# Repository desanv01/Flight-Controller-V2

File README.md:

<h1 align="center">Flight Controller V2</h1>

<p align="center">STM32H743 hardware adaptation and ArduPilot integration</p>

---

STM32H743VIT6 controller adapted from an open-hardware reference design for externally regulated power, a signal-only OpenESC interface, exact Nano-Fit integration and a pinned ArduPilot target. The repository preserves the hardware adaptation, firmware work and vendor engineering packages.

**Project contributor:** [Desan Vasu](https://github.com/desanv01). Project engineering activities were performed by Desan; physical fabrication was external. Documented development: 26 August–6 October 2026. These are evidence dates, not employment dates.

> **Current status:** Engineering prototype. Manufacturer data, a pinned firmware target and freshly built FCV2 bootloader/BIN/APJ are available; powered-board, sensor and flight qualification remain pending.

**Quick links:** [KiCad project](hardware/Flight%20Controller.kicad_pro) · [Schematic PDF](docs/exports/schematic.pdf) · [Manufacturing](fabrication/README.md) · [Development history](docs/development/timeline.md) · [Verification](docs/validation-status.md) · [Releases](https://github.com/desanv01/Flight-Controller-V2/releases)

V2 is derived from [upstream hardware](https://api.github.com/repositories/1095062995), archived commit `0a60da1767061623549253d3cef8649f93ea052c`. Its original hardware design and contributors are credited below.

---

## Table of contents

- [Features](#features)
- [Hardware specifications](#hardware-specifications)
- [Architecture](#architecture)
- [Pin mapping](#pin-mapping)
- [Board layout and wiring](#board-layout-and-wiring)
- [Development history](#development-history)
- [Design and manufacturing files](#design-and-manufacturing-files)
- [Getting started](#getting-started)
- [Firmware](#firmware)
- [Verification](#verification)
- [Repository structure](#repository-structure)
- [License and credits](#license-and-credits)

---

## Features

- Reference-derived STM32H743VIT6 hardware with two dissimilar IMUs
- ICM42688P on SPI6, BMI270 on SPI3 and BMP388 on I2C2
- External regulated POWER1 supply; USB remains data/debug only
- Onboard AP63205 supply path removed; four signal-only OpenESC outputs
- Exact Molex Nano-Fit 105311-1202 on an integral connector tab
- Analog OSD hardware retained, disabled by initial firmware defaults
- Pinned ArduPilot Copter 4.7.1 source and neutral FCV2 target
- Separate JLCPCB and PCBWay source/manufacturing snapshots

---

## Hardware specifications

<details>
<summary>Full specifications and engineering status</summary>

| Parameter | Value |
|---|---|
| MCU | STM32H743VIT6, LQFP100 |
| PCB | 6 copper layers, 1.60 mm nominal |
| Design tool | KiCad 10.0.6 |
| Primary IMU | ICM-42688-P |
| Secondary IMU | BMI270 |
| Barometer | BMP388 |
| Power | External regulated input; exact boundary in power-and-interfaces documentation |
| USB | Data/debug; external controller power required |
| Motor signals | 4 controlled outputs |
| CAN | Retained CAN hardware; runtime qualification pending |
| Storage | W25Q128 flash |
| Board body | 40.5 × 40.5 mm main body |
| Mounting | 30.5 × 30.5 mm M3 |
| Overall envelope | About 40.575 × 50.500 mm including connector tab (vendor record) |
| Clock | 8 MHz active oscillator; HSE bypass |
| Fabrication status | Engineering data available; vendor/physical qualification outstanding |

</details>

Specifications describe the design intent and source. Runtime capabilities require physical qualification; see [validation status](docs/validation-status.md).

---

## Architecture

```mermaid
flowchart LR
    POWER[External regulated supply] --> FC[STM32H743 flight controller]
    IMU[ICM42688P, BMI270 and BMP388] --> FC
    RC[CRSF receiver] --> FC
    GPS[External GNSS and compass] --> FC
    FC -->|Motor signals and ground| ESC[OpenESC]
    BAT[Battery and power distribution] --> ESC
    COMP[Separately powered companion] <-->|Advisory data interface| FC
    USB[USB data and debug] <--> FC
```

The controller owns stabilization, motor waveforms, arming and failsafe. Companion perception/navigation is advisory and separately powered. [Architecture and boundaries](docs/architecture.md).

---

## Pin mapping

Controlled J6 motor outputs map to PE14, PE13, PE11 and PE9 / TIM1. ICM42688P uses SPI6; BMI270 uses SPI3; BMP388 uses I2C2. [Resource matrix](docs/pin-mapping.md).

The [connector pin tables](docs/connector-pinouts.md) are generated from the exact public netlist. Do not infer connector numbering from another version or from an unlabelled photograph.

---

## Board layout and wiring

CAD renders above represent the published source, not photographs of tested hardware. [PCB layer and assembly exports](docs/exports/README.md) · [Power and interfaces](docs/power-and-interfaces.md) · [Bring-up procedure](docs/bring-up.md).

---

## Development history

The [timeline](docs/development/timeline.md) follows requirements, resource freeze, schematic capture, correction, placement, routing and manufacturing stages. Each milestone links its evidence and tag. Publication commits use their actual import date; historical dates remain in the records.

The [development archive](archive/README.md) preserves unique CAD experiments and engineering scripts, including failed approaches. Source fragments are labelled as fragments; no missing historical source state is fabricated.

---

## Design and manufacturing files

| Material | Location |
|---|---|
| Editable current KiCad source | [hardware/](hardware/README.md) |
| Browser-readable schematic and PCB drawings | [docs/exports/](docs/exports/README.md) |
| JLCPCB engineering source and assembly data | [fabrication/jlcpcb/](fabrication/jlcpcb/README.md) |
| PCBWay engineering source and assembly data | [fabrication/pcbway/](fabrication/pcbway/README.md) |
| Downloadable source-associated bundles | [Engineering releases](https://github.com/desanv01/Flight-Controller-V2/releases) |
| Historical sources and experiments | [Archive index](archive/README.md) |

Choose one version and vendor package as a complete set. Do not mix source, Gerbers, BOM or placement files across packages. New public manifests replace original private-package hashes after neutral naming and metadata changes.

---

## Getting started

1. Download or clone this repository.
2. Install KiCad 10 with its standard symbol, footprint and 3D libraries.
3. Open [Flight Controller.kicad_pro](hardware/Flight%20Controller.kicad_pro), then the root schematic and PCB.
4. Review [hardware instructions](hardware/README.md), [verification](docs/validation-status.md) and the correct [vendor package](fabrication/README.md).
5. Review the props-off [bring-up checklist](docs/bring-up.md) before any powered hardware work.

Build/flash guidance for the neutral FCV2 target is in [firmware/README.md](firmware/README.md). Keep initial runtime defaults and the unreserved board-ID limitation visible.

---

## Firmware

ArduPilot Copter 4.7.1 source is pinned to `dbe792162d06cab66c3475fd5556bf7a120f119e`. The [firmware directory](firmware/README.md) contains FCV2 target/defaults, reproducible build instructions, and the successful build logs, binary hashes and downloadable bootloader/BIN/APJ. Legacy upstream targets are historical; final EVT1 compatibility is not asserted.

---

## Verification

Fresh source checks: **14 October 2026**, KiCad **10.0.6**.

| Check | Result |
|---|---|
| ERC errors / warnings | 0 / 40 |
| DRC rule errors / warnings | 0 / 0 |
| Raw unconnected entries | 0 |
| Schematic parity issues | 0 |
| Physical qualification | Pending |

Publication metadata reconciliation removed the original 119 schematic/PCB parity warnings without changing pad, routing, placement, zone or outline geometry.

Ignored checker categories and warning dispositions are recorded in [validation status](docs/validation-status.md). EDA checks and a firmware build do not establish physical reliability or flight qualification.

---

## Repository structure

```text
hardware/       Current coherent KiCad source and libraries
firmware/       Target availability, configuration and build provenance
fabrication/    Vendor-specific source, assembly data and export instructions
docs/           Architecture, pinouts, development history and portfolio case study
media/          Exact-source CAD renders and layer views
verification/   Fresh native reports, corrections and exception evidence
tools/          Portable checking/export utilities
archive/        Recovered source states and indexed development experiments
```

---

## License and credits

Inherited upstream hardware source remains under [CERN-OHL-S-2.0](LICENSE). KiCad-derived libraries, ArduPilot and other third-party content retain their own notices. [Third-party notices](THIRD_PARTY_NOTICES.md).

Desan Vasu performed the project engineering activities; fabrication was external. [Contribution statement](CONTRIBUTIONS.md) · [Portfolio case study](docs/portfolio/case-study.md).

Reference projects: [ArduPilot](https://github.com/ArduPilot/ardupilot), [KiCad](https://www.kicad.org/), and the OpenESC/OpenRX ecosystem identified in the source records.

Related project: [Flight Controller V1](https://github.com/desanv01/Flight-Controller-V1).

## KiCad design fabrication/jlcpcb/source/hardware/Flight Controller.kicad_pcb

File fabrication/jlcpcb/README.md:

# Flight Controller V2 — JLCPCB engineering package

Status: engineering data available; physical qualification pending. Supplier construction/impedance, actual part sourcing, rotations and fabricated-article tests remain external.

## Source and fabrication

Exact source: `source/hardware/`. [Source manifest](source/source-manifest.json). [Fresh source checks](verification/summary.json). Regenerated neutral Gerbers/drills are in `fabrication/`; upload the Gerber/drill-only ZIP rather than a documentation archive. Technical source and electrical/placement geometry are preserved; visible naming and descriptive metadata were updated for publication.

## Assembly files

- [FC_EVT1-BOM.csv](assembly/reference/FC_EVT1-BOM.csv)
- [FC_EVT1-CPL-JLCPCB.csv](assembly/reference/FC_EVT1-CPL-JLCPCB.csv)
- [FC_EVT1-CPL-KiCad.csv](assembly/reference/FC_EVT1-CPL-KiCad.csv)
- [FC_EVT1-JLCPCB-BOM-FINAL.csv](assembly/FC_EVT1-JLCPCB-BOM-FINAL.csv)
- [FC_EVT1-JLCPCB-CPL-FINAL.csv](assembly/FC_EVT1-JLCPCB-CPL-FINAL.csv)
- [J12-HAND-INSTALL-BOM.csv](assembly/J12-HAND-INSTALL-BOM.csv)

For V2 JLCPCB, files ending BOM-FINAL and CPL-FINAL are the final reconciled SMT pair; J12 is separately hand-installed. Earlier raw/engineering files are preserved only for traceability.

Use this vendor's exact BOM and centroid. Confirm rotation and sourcing with the manufacturer. J12 in V1 is microSD; J12 in V2 is POWER1, so designators must not be transferred between versions. [Current connector nets](../../docs/connector-pinouts.md).

## Documentation

Readable neutral exports are in `exports/`. Historical manufacturer notes in `documents/` retain original technical intent but some file references predate publication restructuring; use this README and exact source manifest as the upload map. [Physical checklist](../../docs/bring-up.md).

## Definitive upload map

| Supplier field | Public file |
|---|---|
| PCB fabrication | [Gerber/drill-only ZIP](fabrication/Gerber-Drill-Upload.zip) |
| Assembly BOM | [FC_EVT1-JLCPCB-BOM-FINAL.csv](assembly/FC_EVT1-JLCPCB-BOM-FINAL.csv) |
| SMT placement | [FC_EVT1-JLCPCB-CPL-FINAL.csv](assembly/FC_EVT1-JLCPCB-CPL-FINAL.csv) |
| Assembly drawing | [Assembly PDF](exports/assembly.pdf) |
| Fabrication drawing | [Fabrication PDF](exports/fabrication.pdf) |
| Schematic | [Schematic PDF](exports/schematic.pdf) |

Fresh reconciliation: 51 BOM rows, 113 BOM references and 113 placement references. Placement-only references: zero. BOM-only references: `none`; these require the separate THT/manual instructions. [Pair report](verification/final-upload-pair.json).

Raw export files under `assembly/reference/` are retained for traceability and are not the supplier upload pair. Part sourcing/rotation/vendor CAM and physical qualification are still required.

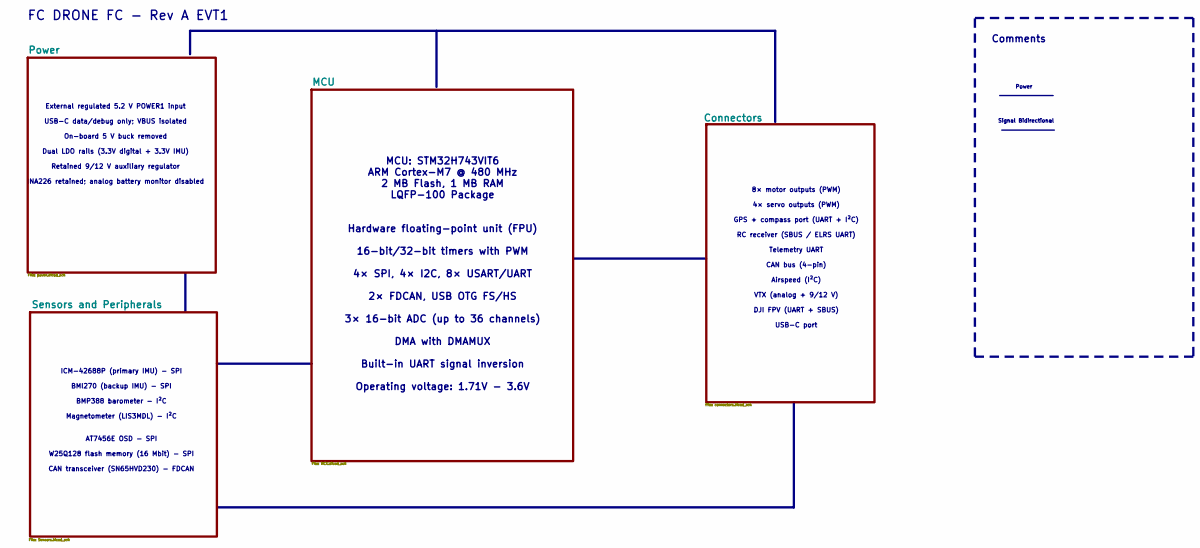
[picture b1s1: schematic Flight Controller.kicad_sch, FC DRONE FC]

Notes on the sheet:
FC DRONE FC - Rev A EVT1
ICM-42688P (primary IMU) - SPI BMI270 (backup IMU) - SPI BMP388 barometer - I²C Magnetometer (LIS3MDL) - I²C AT7456E OSD - SPI W25Q128 flash memory (16 Mbit) - SPI CAN transceiver (SN65HVD230) - FDCAN
Signal Bidirectional
8× motor outputs (PWM) 4× servo outputs (PWM) GPS + compass port (UART + I²C) RC receiver (SBUS / ELRS UART) Telemetry UART CAN bus (4-pin) Airspeed (I²C) VTX (analog + 9/12 V) DJI FPV (UART + SBUS) USB-C port
Comments
External regulated 5.2 V POWER1 input USB-C data/debug only; VBUS isolated On-board 5 V buck removed Dual LDO rails (3.3V digital + 3.3V IMU) Retained 9/12 V auxiliary regulator INA226 retained; analog battery monitor disabled
MCU: STM32H743VIT6 ARM Cortex-M7 @ 480 MHz 2 MB Flash, 1 MB RAM LQFP-100 Package Hardware floating-point unit (FPU) 16-bit/32-bit timers with PWM 4× SPI, 4× I2C, 8× USART/UART 2× FDCAN, USB OTG FS/HS 3× 16-bit ADC (up to 36 channels) DMA with DMAMUX Built-in UART signal inversion Operating voltage: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
Power

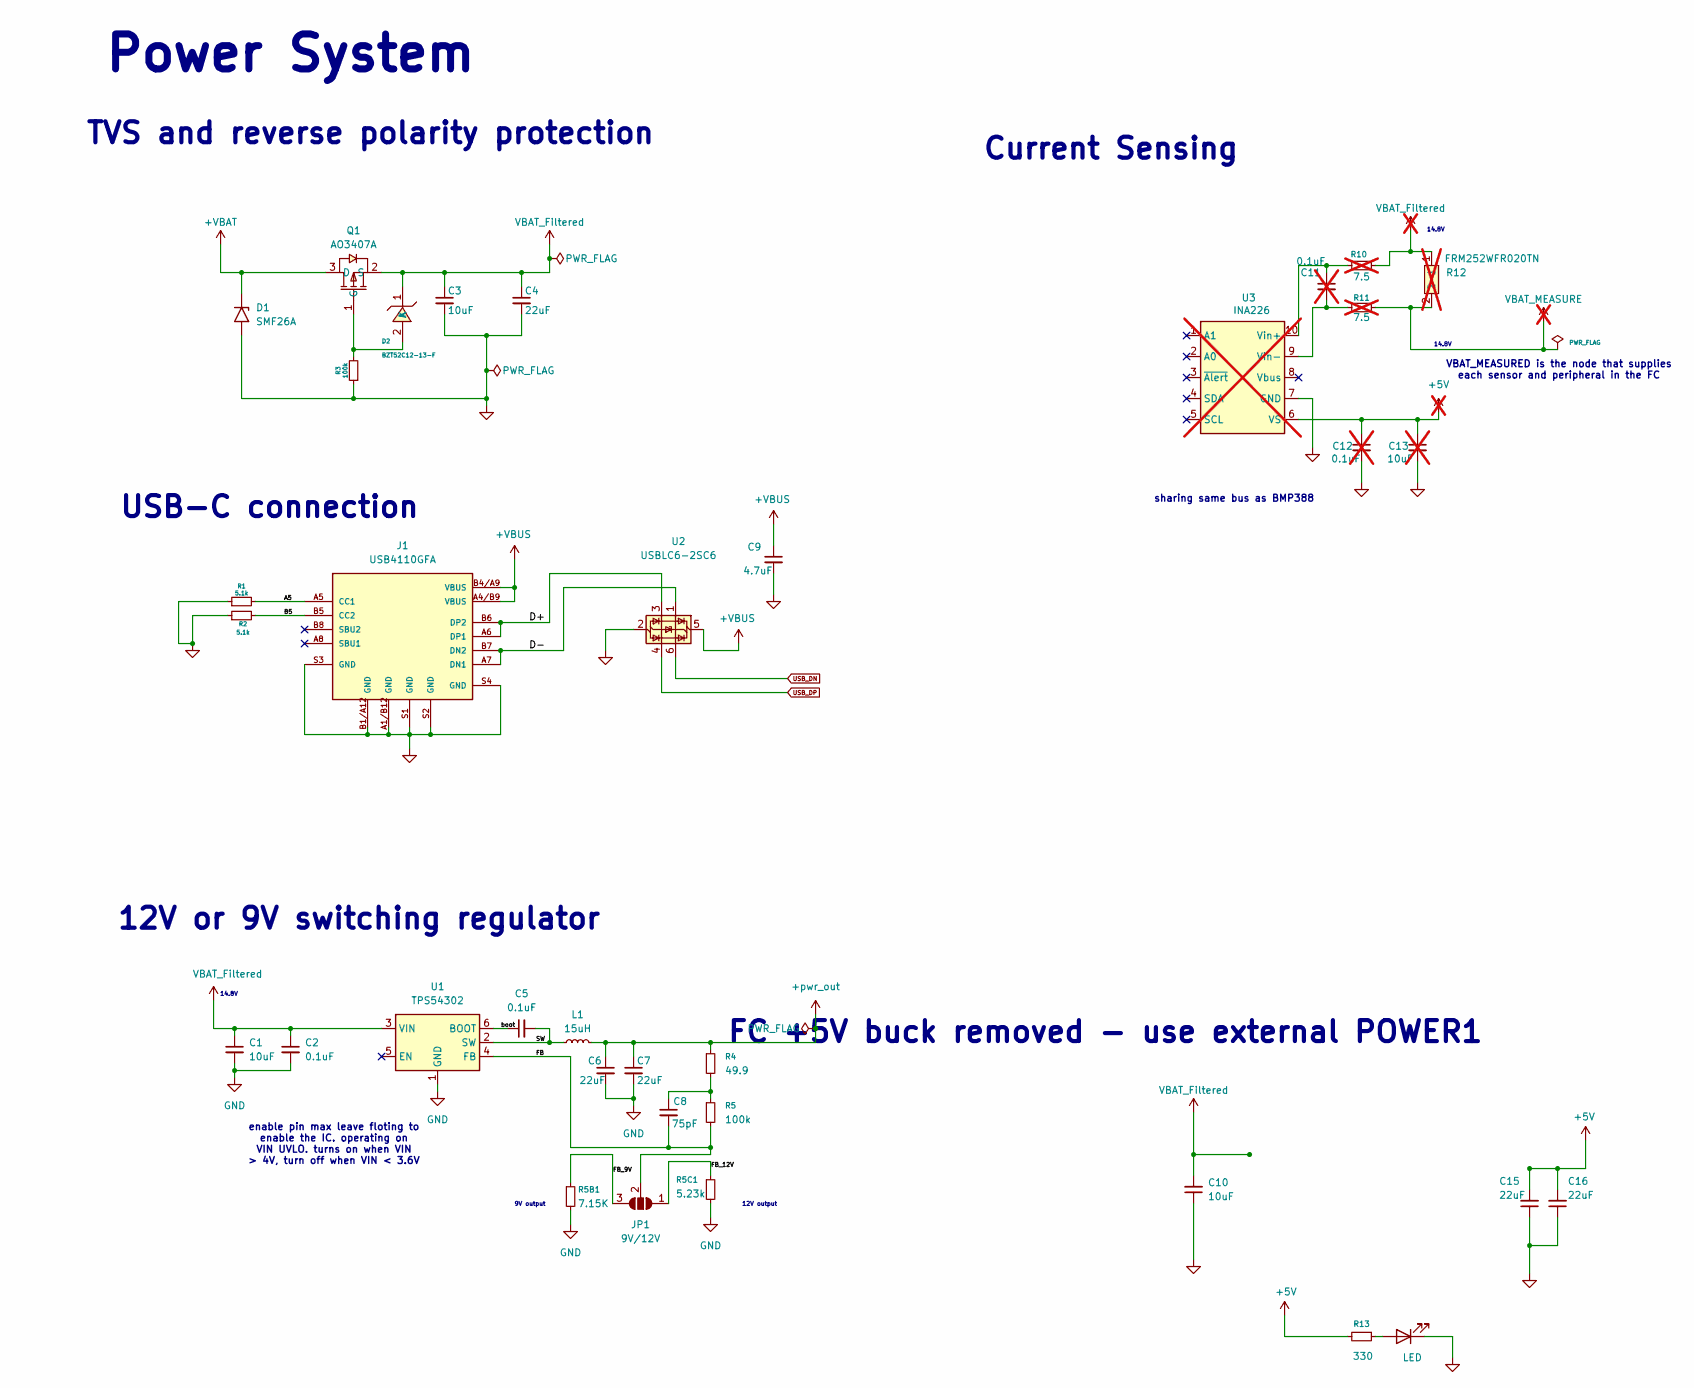
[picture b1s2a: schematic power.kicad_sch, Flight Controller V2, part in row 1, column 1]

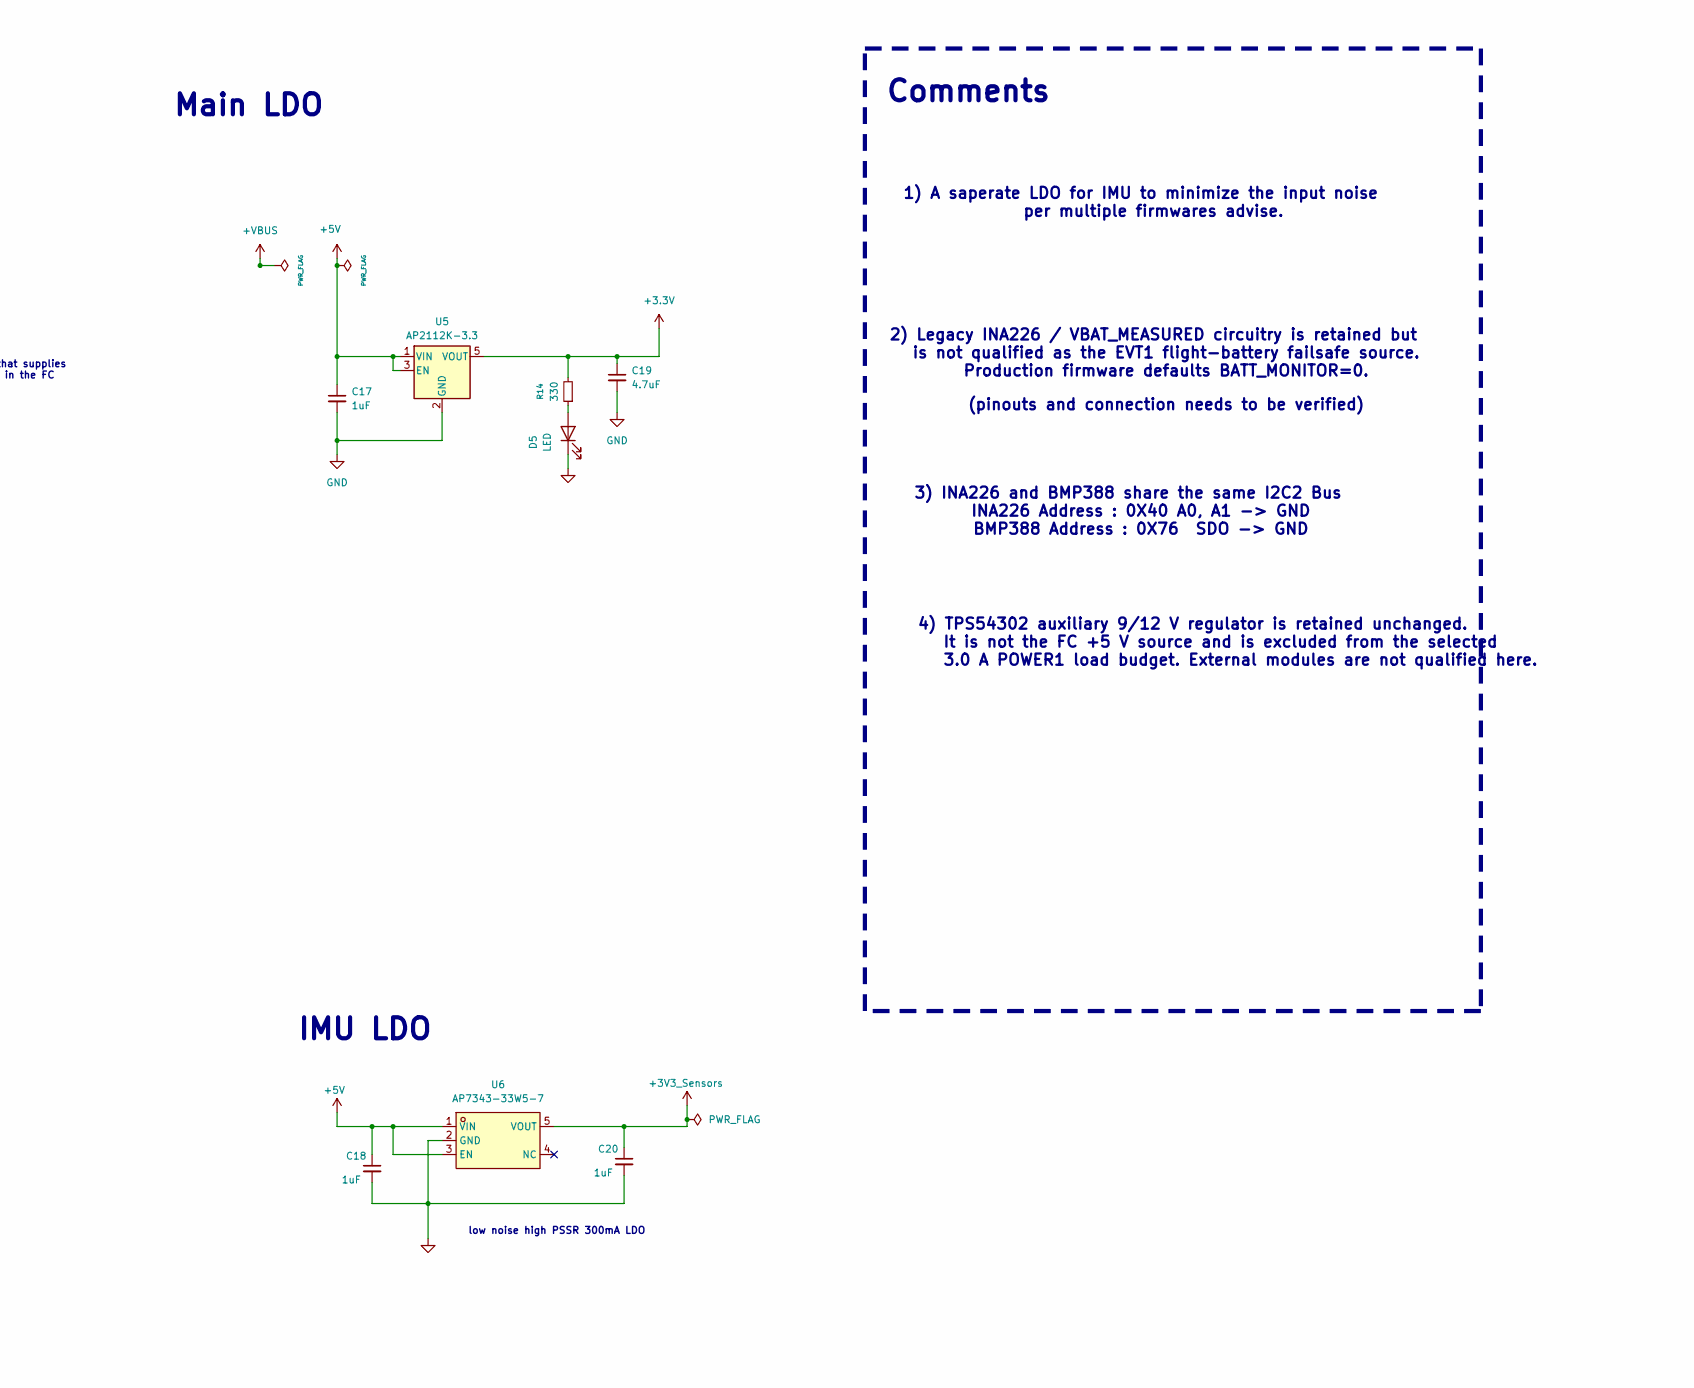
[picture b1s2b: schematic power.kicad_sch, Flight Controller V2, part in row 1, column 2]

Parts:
C1, C3, C10: 10uF; C_0603_1608Metric
C2, C5: 0.1uF; C_0402_1005Metric
C4: 22uF; C_0805_2012Metric
C6, C7, C15, C16: 22uF; C_0603_1608Metric
C8: 75pF; C_0402_1005Metric
C9: 4.7uF; C_0402_1005Metric
C11, C12: 0.1uF; C_0603_1608Metric; not fitted
C13: 10uF; C_0805_2012Metric; not fitted
C17, C18, C20: 1uF; C_0603_1608Metric
C19: 4.7uF; C_0603_1608Metric
D1: SMF26A; D_SMF
D2: BZT52C12-13-F; (zener)SOD-123F_L2.8-W1.8-LS3.7-RD; LCSC Part C177013
D4, D5: LED; LED_0805_2012Metric
J1: USB4110GFA; GCT_USB4110GFA
JP1: 9V/12V; SolderJumper-3_P1.3mm_Open_RoundedPad1.0x1.5mm_NumberLabels
L1: 15uH; IND-SMD_L5.4-W5.2
Q1: AO3407A; LCSC Part C15155
R1, R2: 5.1k; R_0402_1005Metric
R3, R5: 100k; R_0402_1005Metric
R4: 49.9; R_0402_1005Metric
R5B1: 7.15K; R_0402_1005Metric
R5C1: 5.23k; R_0402_1005Metric
R10, R11: 7.5; R_0402_1005Metric; not fitted
R12: FRM252WFR020TN; R2512; LCSC Part C7420049; not fitted
R13, R14: 330; R_0402_1005Metric
U1: TPS54302; SOT-23-6
U2: USBLC6-2SC6; SOT-23-6
U3: INA226; VSSOP-10_3x3mm_P0.5mm; not fitted
U5: AP2112K-3.3; SOT-23-5
U6: AP7343-33W5-7; (AP7343 )SOT-25_L3.0-W1.6-P0.95-LS2.8-BL; LCSC Part C460383

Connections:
+3.3V: C19.1, R14.2, U5.5 (VOUT); also elsewhere on the board
+3V3_Sensors: C20.1, U6.5 (VOUT); also elsewhere on the board
+5V: C12.1, C13.1, C15.2, C16.2, C17.1, C18.1, R13.2, U3.6 (VS), U5.1 (VIN), U5.3 (EN), U6.1 (VIN), U6.3 (EN); also elsewhere on the board
+VBAT: D1.1 (A1), Q1.3 (D); also elsewhere on the board
+VBUS: C9.1, J1.A4/B9 (VBUS), J1.B4/A9 (VBUS), U2.5 (VBUS)
+pwr_out: C6.1, C7.1, L1.2, R4.1; also elsewhere on the board
/Power/A5: J1.A5 (CC1), R1.2
/Power/B5: J1.B5 (CC2), R2.2
/Power/D+: J1.A6 (DP1), J1.B6 (DP2), U2.3 (I/O2)
/Power/D-: J1.A7 (DN1), J1.B7 (DN2), U2.1 (I/O1)
/Power/FB: C8.2, JP1.2 (C), R5.2, U1.4 (FB)
/Power/FB_9V: JP1.3 (B), R5B1.1
/Power/FB_12V: JP1.1 (A), R5C1.1
/Power/SW: C5.2, L1.1, U1.2 (SW)
/Power/boot: C5.1, U1.6 (BOOT)
GND: C1.2, C2.2, C3.2, C4.2, C6.2, C7.2, C9.2, C10.1, C12.2, C13.2, C15.1, C16.1, C17.2, C18.2, C19.2, C20.2, D1.2 (A2), D4.1 (K), D5.1 (K), J1.A1/B12 (GND), J1.B1/A12 (GND), J1.S1 (GND), J1.S2 (GND), J1.S3 (GND), J1.S4 (GND), R1.1, R2.1, R3.1, R5B1.2, R5C1.2, U1.1 (GND), U2.2 (GND), U3.7 (GND), U5.2 (GND), U6.2 (GND); also elsewhere on the board
unnamed: C8.1, R4.2, R5.1
unnamed: C11.1, R10.1, U3.10 (Vin+)
unnamed: C11.2, R11.1, U3.9 (Vin-)
unnamed: D2.2 (A), Q1.1 (G), R3.2
unnamed: D4.2 (A), R13.1
unnamed: D5.2 (A), R14.1
unnamed: R11.2, R12.2
USB_DN: U2.6 (I/O1); also elsewhere on the board
USB_DP: U2.4 (I/O2); also elsewhere on the board
VBAT_Filtered: C1.1, C2.1, C3.1, C4.1, C10.2, D2.1 (K), Q1.2 (S), R10.2, R12.1, U1.3 (VIN)

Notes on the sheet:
FC +5V buck removed - use external POWER1
Power System
2) Legacy INA226 / VBAT_MEASURED circuitry is retained but is not qualified as the EVT1 flight-battery failsafe source. Production firmware defaults BATT_MONITOR=0.
low noise high PSSR 300mA LDO
(pinouts and connection needs to be verified)
VBAT_MEASURED is the node that supplies each sensor and peripheral in the FC
9V output
12V output
IMU LDO
TVS and reverse polarity protection
4) TPS54302 auxiliary 9/12 V regulator is retained unchanged. It is not the FC +5 V source and is excluded from the selected 3.0 A POWER1 load budget. External modules are not qualified here.
sharing same bus as BMP388
Comments
3) INA226 and BMP388 share the same I2C2 Bus INA226 Address : 0X40 A0, A1 -> GND BMP388 Address : 0X76 SDO -> GND
14.8V
Current Sensing
12V or 9V switching regulator
USB-C connection
1) A saperate LDO for IMU to minimize the input noise per multiple firmwares advise.
Main LDO
enable pin max leave floting to enable the IC. operating on VIN UVLO. turns on when VIN > 4V, turn off when VIN < 3.6V

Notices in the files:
fabrication/jlcpcb/source/hardware/Flight Controller.kicad_sch:
Derived from upstream commit 0a60da1 under CERN-OHL-S-2.0
